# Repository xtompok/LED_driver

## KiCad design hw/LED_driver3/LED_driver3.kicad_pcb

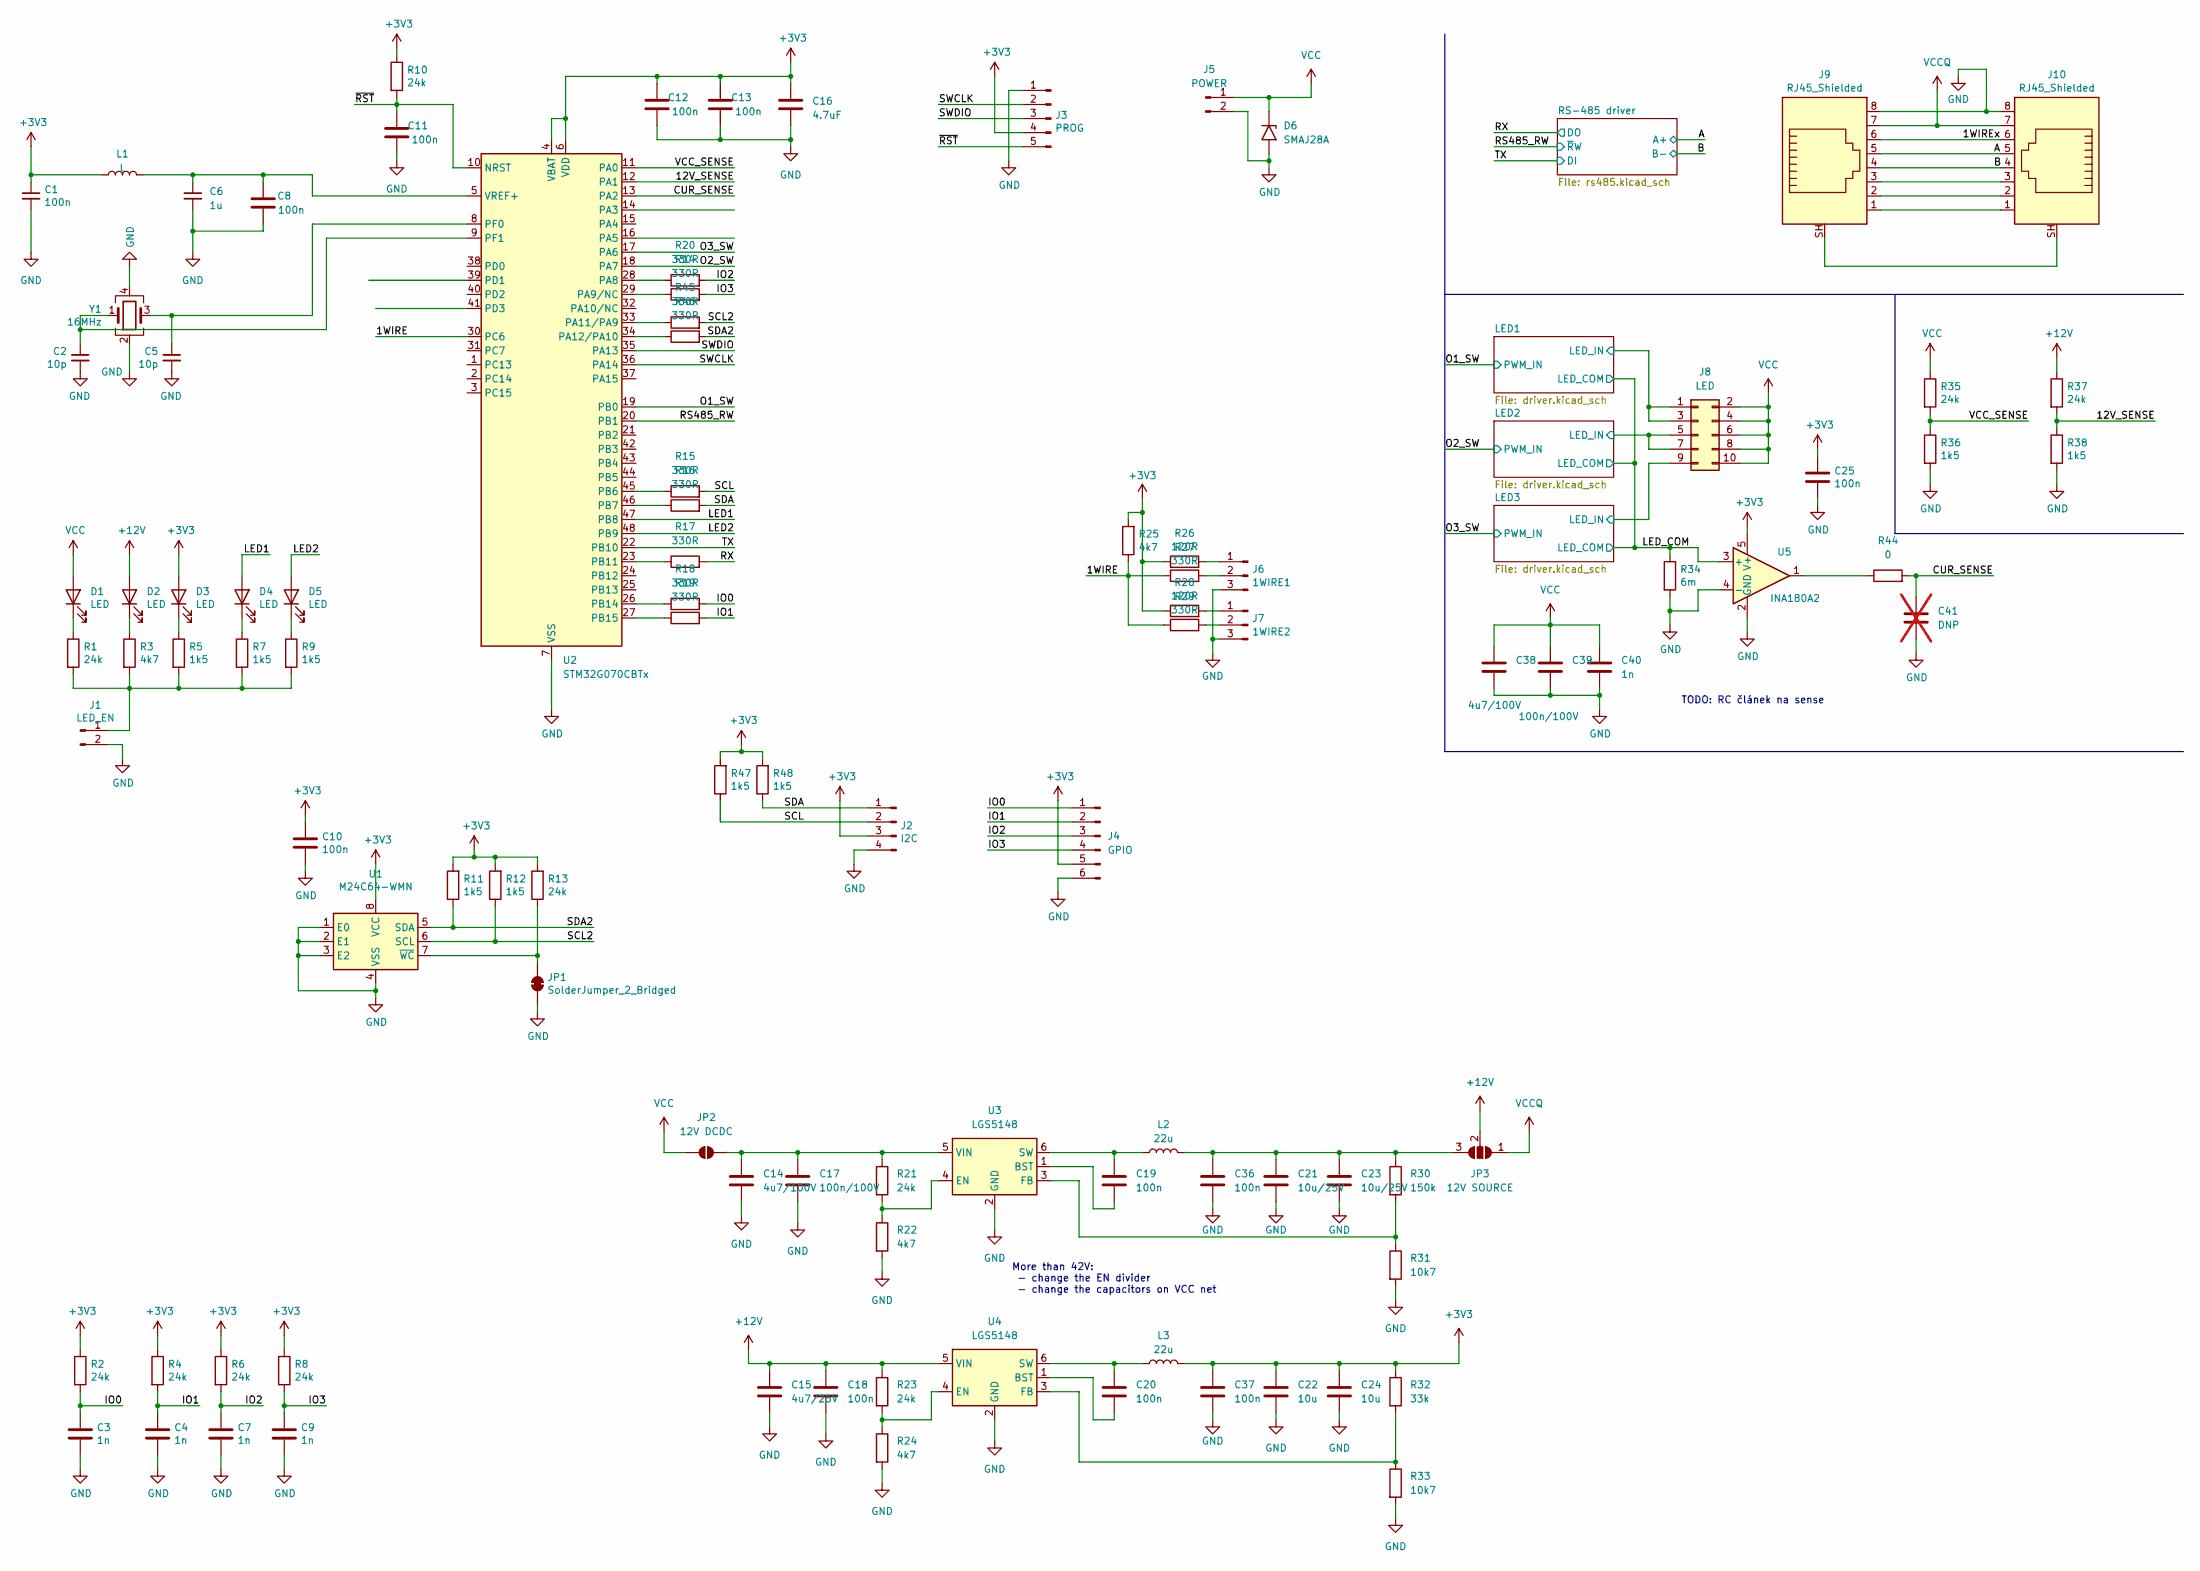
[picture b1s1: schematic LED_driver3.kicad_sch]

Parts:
C1: 100n; C_0603_1608Metric; Manufacturer_Part_Number CC0603KRX7R9BB104; LCSC C14663
C2, C5: 10p; C_0402_1005Metric; LCSC C32949
C3, C4, C7, C9, C40: 1n; C_0603_1608Metric; LCSC C1588
C6: 1u; C_0805_2012Metric; Manufacturer_Part_Number CL21B105KBFNNNE; LCSC C28323
C8, C10, C11, C12, C13, C18, C19, C20, C25, C36, C37: 100n; C_0603_1608Metric; LCSC C14663
C14, C38: 4u7/100V; C_1206_3216Metric; LCSC C29823
C15: 4u7/25V; C_0805_2012Metric; LCSC C1779
C16: 4.7uF; C_0603_1608Metric; LCSC C19666
C17, C39: 100n/100V; C_0805_2012Metric; LCSC C28233
C21, C23: 10u/25V; C_0805_2012Metric; LCSC C440198
C22, C24: 10u; C_0805_2012Metric; LCSC C440198
C41: DNP; C_0603_1608Metric; not fitted
D1: LED; LED_0603_1608Metric; LCSC C72043
D2, D3, D4, D5: LED; LED_0603_1608Metric
D6: SMAJ28A; D_SMA; LCSC C908775
J1: LED_EN; SolderJumper-2_P1.3mm_Open_TrianglePad1.0x1.5mm
J2: I2C; 15EDGVC-2.5-04P-14
J3: PROG; Molex_KK-254_AE-6410-05A_1x05_P2.54mm_Vertical
J4: GPIO; 15EDGVC-2.5-06P-14
J5: POWER; PhoenixContact_MSTB_2,5_2-GF-5,08_1x02_P5.08mm_Horizontal_T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
J6: 1WIRE1; 15EDGVC-2.5-03P-14
J7: 1WIRE2; 15EDGVC-2.5-03P-14
J8: LED; 15EDGRHCM-THR-3,50-10P-13
J9, J10: RJ45_Shielded; RJJS-88-A22-E1V
JP1: SolderJumper_2_Bridged; SolderJumper-2_P1.3mm_Bridged_Pad1.0x1.5mm
JP2: 12V DCDC; SolderJumper-2_P1.3mm_Open_TrianglePad1.0x1.5mm
JP3: 12V SOURCE; SolderJumper-3_P2.0mm_Open_TrianglePad1.0x1.5mm
L1: L; L_0805_2012Metric; LCSC C88990
L2, L3: 22u; L_Sunlord_SWPA4030S; LCSC C83472
R1, R2, R4, R6, R8, R10, R13, R21, R23, R35, R37: 24k; R_0603_1608Metric; LCSC C23352
R3, R22, R24, R25: 4k7; R_0603_1608Metric; LCSC C23162
R5, R7, R9, R11, R12, R36, R38, R47, R48: 1k5; R_0603_1608Metric; LCSC C22843
R14, R15, R16, R17, R18, R19, R20, R27, R29, R45, R46: 330R; R_0603_1608Metric; LCSC C23138
R26, R28: 120R; R_0603_1608Metric; LCSC C22787
R30: 150k; R_0603_1608Metric
R31, R33: 10k7; R_0603_1608Metric
R32: 33k; R_0603_1608Metric
R34: 6m; R_2512_6332Metric; LCSC C728340
R44: 0; R_0603_1608Metric
U1: M24C64-WMN; SOIC-8_3.9x4.9mm_P1.27mm; LCSC C79988
U2: STM32G070CBTx; LQFP-48_7x7mm_P0.5mm; LCSC C529338
U3, U4: LGS5148; SOT-23-6
U5: INA180A2; SOT-23-5; LCSC C192764
Y1: 16MHz; Crystal_SMD_3225-4Pin_3.2x2.5mm; LCSC C13738

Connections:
+3V3: C1.1, C10.1, C12.1, C13.1, C16.1, C22.1, C24.1, C25.1, C37.1, D3.2 (A), J2.3, J3.4, J4.5, L1.1, L3.2, R2.1, R4.1, R6.1, R8.1, R10.1, R11.2, R12.2, R13.2, R25.2, R26.1, R28.1, R32.1, R47.2, R48.2, U1.8 (VCC), U2.4 (VBAT), U2.6 (VDD), U5.5 (V+); also elsewhere on the board
+12V: C15.1, C18.1, D2.2 (A), JP3.2 (C), R23.1, R37.1, U4.5 (VIN); also elsewhere on the board
/1WIRE: R25.1, R27.1, R29.1, U2.30 (PC6)
/1WIREx: J9.6, J10.6
/12V_SENSE: R37.2, R38.1, U2.12 (PA1)
/A: J9.5, J10.5; also elsewhere on the board
/B: J9.4, J10.4; also elsewhere on the board
/CUR_SENSE: C41.1, R44.2, U2.13 (PA2)
/IO0: C3.2, J4.1, R2.2, R18.2
/IO1: C4.2, J4.2, R4.2, R19.2
/IO2: C7.2, J4.3, R6.2, R20.2
/IO3: C9.2, J4.4, R8.2, R14.2
/LED1: D4.2 (A), U2.47 (PB8)
/LED1/LED_IN: J8.1, J8.3; also elsewhere on the board
/LED2: D5.2 (A), U2.48 (PB9)
/LED2/LED_IN: J8.5, J8.7; also elsewhere on the board
/LED3/LED_IN: J8.9; also elsewhere on the board
/LED_COM: R34.1, U5.3 (+); also elsewhere on the board
/O1_SW: U2.19 (PB0); also elsewhere on the board
/O2_SW: U2.18 (PA7); also elsewhere on the board
/O3_SW: U2.17 (PA6); also elsewhere on the board
/RS485_RW: U2.20 (PB1); also elsewhere on the board
/RX: R17.2; also elsewhere on the board
/SCL: J2.2, R15.2, R47.1
/SCL2: R12.1, R45.2, U1.6 (SCL)
/SDA: J2.1, R16.2, R48.1
/SDA2: R11.1, R46.2, U1.5 (SDA)
/SWCLK: J3.2, U2.36 (PA14)
/SWDIO: J3.3, U2.35 (PA13)
/TX: U2.22 (PB10); also elsewhere on the board
/VCC_SENSE: R35.2, R36.1, U2.11 (PA0)
/~RST: C11.1, J3.5, R10.2, U2.10 (NRST)
GND: C1.2, C2.2, C3.1, C4.1, C5.2, C6.2, C7.1, C8.2, C9.1, C10.2, C11.2, C12.2, C13.2, C14.2, C15.2, C16.2, C17.2, C18.2, C21.2, C22.2, C23.2, C24.2, C25.2, C36.2, C37.2, C38.2, C39.2, C40.2, C41.2, D6.2 (A2), J1.2, J2.4, J3.1, J4.6, J5.2, J6.3, J7.3, J9.8, J10.8, JP1.2 (B), R22.2, R24.2, R31.2, R33.2, R34.2, R36.2, R38.2, U1.1 (E0), U1.2 (E1), U1.3 (E2), U1.4 (VSS), U2.7 (VSS), U3.2 (GND), U4.2 (GND), U5.2 (GND), U5.4 (-), Y1.2, Y1.4; also elsewhere on the board
unnamed: D1.1 (K), R1.1
unnamed: D2.1 (K), R3.1
unnamed: D3.1 (K), R5.1
unnamed: D4.1 (K), R7.1
unnamed: D5.1 (K), R9.1
unnamed: J1.1, R1.2, R3.2, R5.2, R7.2, R9.2
unnamed: J6.1, R26.2
unnamed: J6.2, R27.2
unnamed: J7.1, R28.2
unnamed: J7.2, R29.2
unnamed: J9.1, J10.1
unnamed: J9.2, J10.2
unnamed: J9.3, J10.3
unnamed: J9.SH, J10.SH
unnamed: JP1.1 (A), R13.1, U1.7 (~WC)
unnamed: C14.1, C17.1, JP2.2 (B), R21.1, U3.5 (VIN)
unnamed: C21.1, C23.1, C36.1, JP3.3 (B), L2.2, R30.1
unnamed: R44.1, U5.1
unnamed: R20.1, U2.28 (PA8)
unnamed: R14.1, U2.29 (PA9/NC)
unnamed: R45.1, U2.33 (PA11/PA9)
unnamed: R46.1, U2.34 (PA12/PA10)
unnamed: R15.1, U2.45 (PB6)
unnamed: R16.1, U2.46 (PB7)
unnamed: R17.1, U2.23 (PB11)
unnamed: R18.1, U2.26 (PB14)
unnamed: R19.1, U2.27 (PB15)
unnamed: C5.1, U2.8 (PF0), Y1.3
unnamed: C2.1, U2.9 (PF1), Y1.1
unnamed: C6.1, C8.1, L1.2, U2.5 (VREF+)
unnamed: C19.2, U3.1 (BST)
unnamed: R21.2, R22.1, U3.4 (EN)
unnamed: R30.2, R31.1, U3.3 (FB)
unnamed: C19.1, L2.1, U3.6 (SW)
unnamed: C20.2, U4.1 (BST)
unnamed: R23.2, R24.1, U4.4 (EN)
unnamed: R32.2, R33.1, U4.3 (FB)
unnamed: C20.1, L3.1, U4.6 (SW)
VCC: C38.1, C39.1, C40.1, D1.2 (A), D6.1 (A1), J5.1, J8.2, J8.4, J8.6, J8.8, J8.10, JP2.1 (A), R35.1; also elsewhere on the board
VCCQ: J9.7, J10.7, JP3.1 (A)

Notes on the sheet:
More than 42V: - change the EN divider - change the capacitors on VCC net
TODO: RC článek na sense

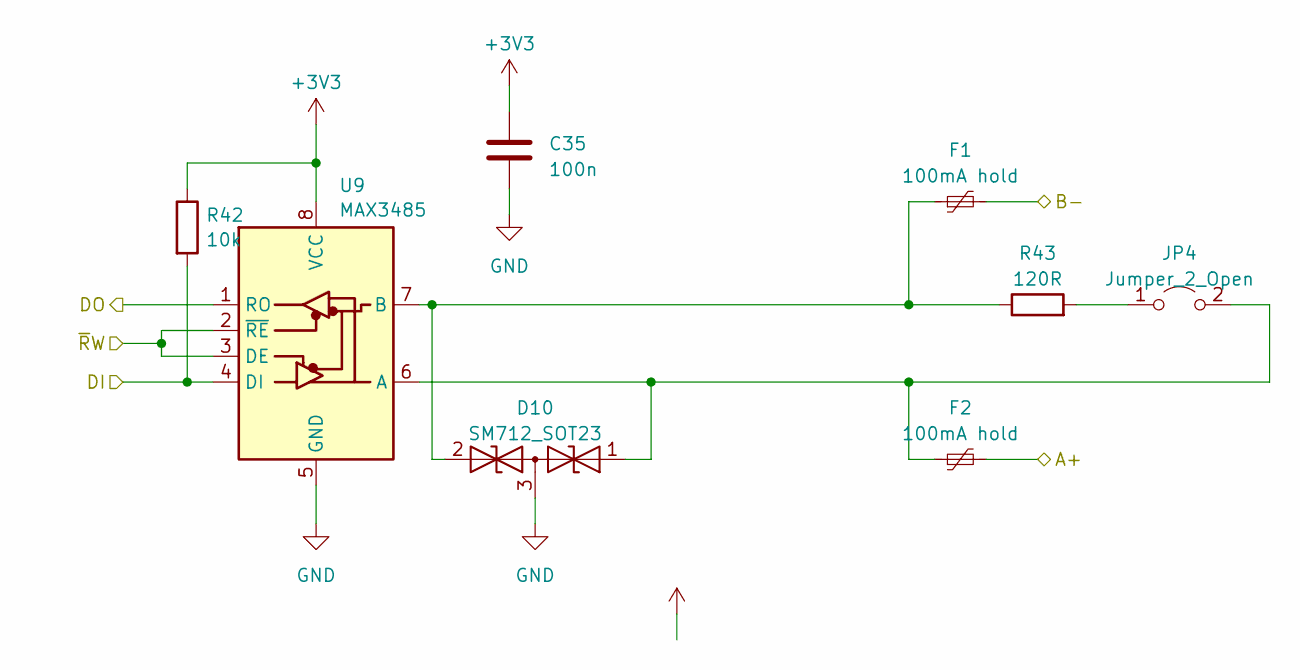
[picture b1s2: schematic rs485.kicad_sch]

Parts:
C35: 100n; C_0603_1608Metric; LCSC C14663
D10: SM712_SOT23; SOT-23; LCSC C404012
F1, F2: 100mA hold; Fuse_1206_3216Metric; LCSC C70065
JP4: Jumper_2_Open; SolderJumper-2_P1.3mm_Open_TrianglePad1.0x1.5mm; LCSC XXXX
R42: 10k; R_0603_1608Metric; LCSC C25804
R43: 120R; R_0603_1608Metric; LCSC C22787
U9: MAX3485; SOIC-8_3.9x4.9mm_P1.27mm; LCSC C8963

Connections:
+3V3: C35.1, R42.1, U9.8 (VCC); also elsewhere on the board
/A: F2.2; also elsewhere on the board
/B: F1.2; also elsewhere on the board
/RS485_RW: U9.2 (~RE), U9.3 (DE); also elsewhere on the board
/RX: U9.1 (RO); also elsewhere on the board
/TX: R42.2, U9.4 (DI); also elsewhere on the board
GND: C35.2, D10.3 (common), U9.5 (GND); also elsewhere on the board
unnamed: D10.1 (A1), F2.1, JP4.2 (B), U9.6 (A)
unnamed: D10.2 (A2), F1.1, R43.1, U9.7 (B)
unnamed: JP4.1 (A), R43.2

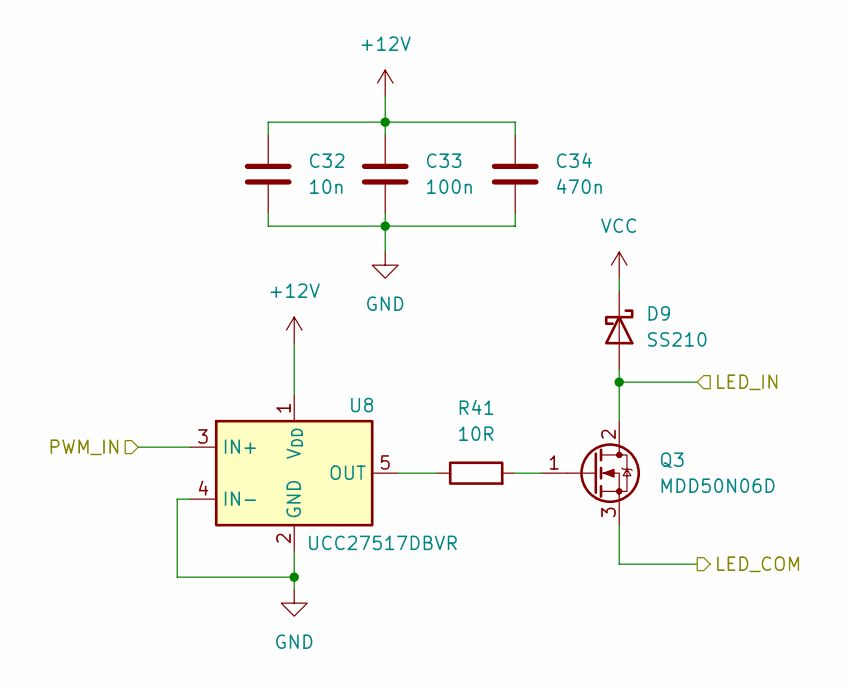
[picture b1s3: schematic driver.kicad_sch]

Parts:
C32: 10n; C_0603_1608Metric; LCSC C57112
C33: 100n; C_0603_1608Metric; LCSC C14663
C34: 470n; C_0603_1608Metric; LCSC C1623
D9: SS210; D_SMA; LCSC C14996
Q3: MDD50N06D; TO-252-2; LCSC C99395
R41: 10R; R_0603_1608Metric; LCSC C22859
U8: UCC27517DBVR; SOT-23-5

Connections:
+12V: C32.1, C33.1, C34.1, U8.1 (V_{DD}); also elsewhere on the board
/LED3/LED_IN: D9.2 (A), Q3.2 (D); also elsewhere on the board
/LED_COM: Q3.3 (S); also elsewhere on the board
/O3_SW: U8.3 (IN+); also elsewhere on the board
GND: C32.2, C33.2, C34.2, U8.2 (GND), U8.4 (IN-); also elsewhere on the board
unnamed: Q3.1 (G), R41.2
unnamed: R41.1, U8.5 (OUT)
VCC: D9.1 (K); also elsewhere on the board

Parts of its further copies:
C26, C29: 10n; C_0603_1608Metric; LCSC C57112
C27, C30: 100n; C_0603_1608Metric; LCSC C14663
C28, C31: 470n; C_0603_1608Metric; LCSC C1623
D7, D8: SS210; D_SMA; LCSC C14996
Q1, Q2: MDD50N06D; TO-252-2; LCSC C99395
R39, R40: 10R; R_0603_1608Metric; LCSC C22859
U6, U7: UCC27517DBVR; SOT-23-5

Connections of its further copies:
+12V: C26.1, C27.1, C28.1, C29.1, C30.1, C31.1, U6.1 (V_{DD}), U7.1 (V_{DD}); also elsewhere on the board
/LED1/LED_IN: D7.2 (A), Q1.2 (D); also elsewhere on the board
/LED2/LED_IN: D8.2 (A), Q2.2 (D); also elsewhere on the board
/LED_COM: Q1.3 (S), Q2.3 (S); also elsewhere on the board
/O1_SW: U6.3 (IN+); also elsewhere on the board
/O2_SW: U7.3 (IN+); also elsewhere on the board
GND: C26.2, C27.2, C28.2, C29.2, C30.2, C31.2, U6.2 (GND), U6.4 (IN-), U7.2 (GND), U7.4 (IN-); also elsewhere on the board
unnamed: Q1.1 (G), R39.2
unnamed: Q2.1 (G), R40.2
unnamed: R39.1, U6.5 (OUT)
unnamed: R40.1, U7.5 (OUT)
VCC: D7.1 (K), D8.1 (K); also elsewhere on the board

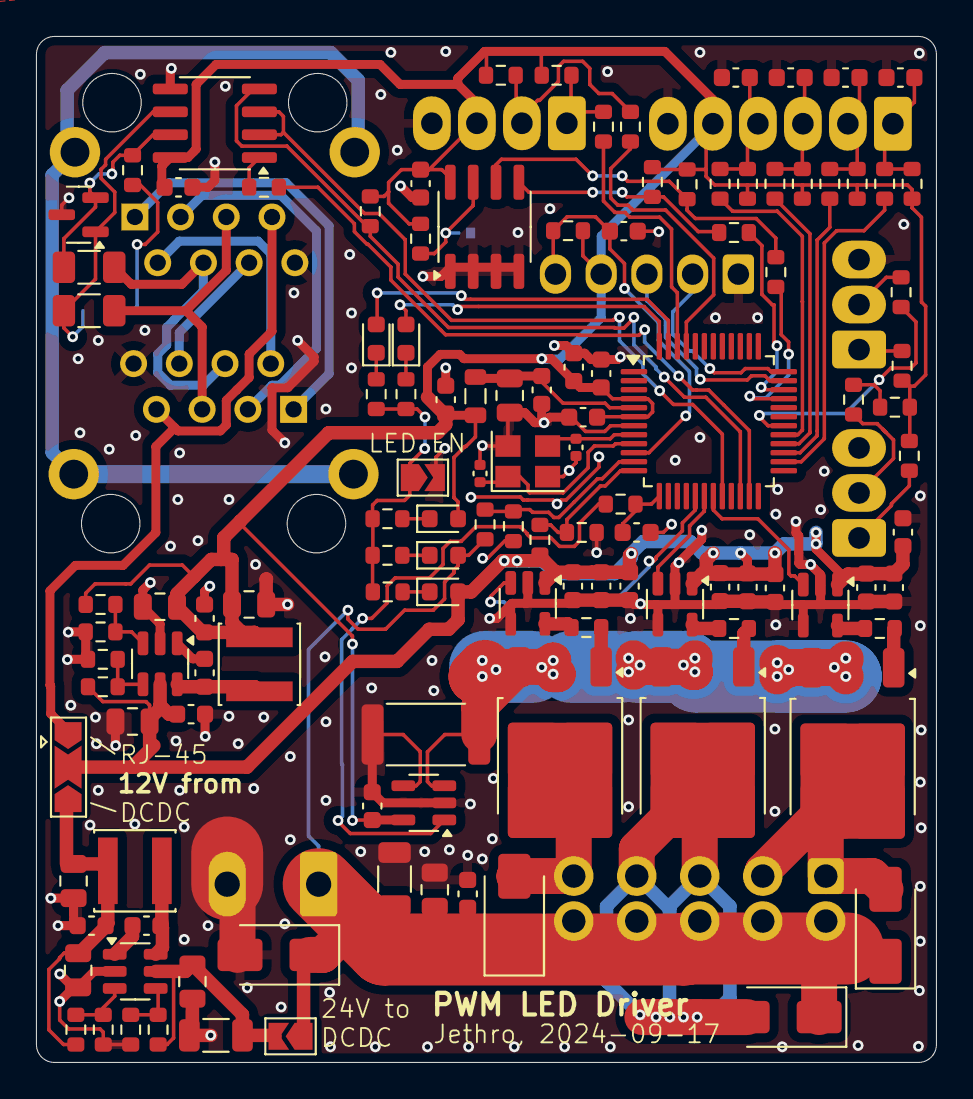
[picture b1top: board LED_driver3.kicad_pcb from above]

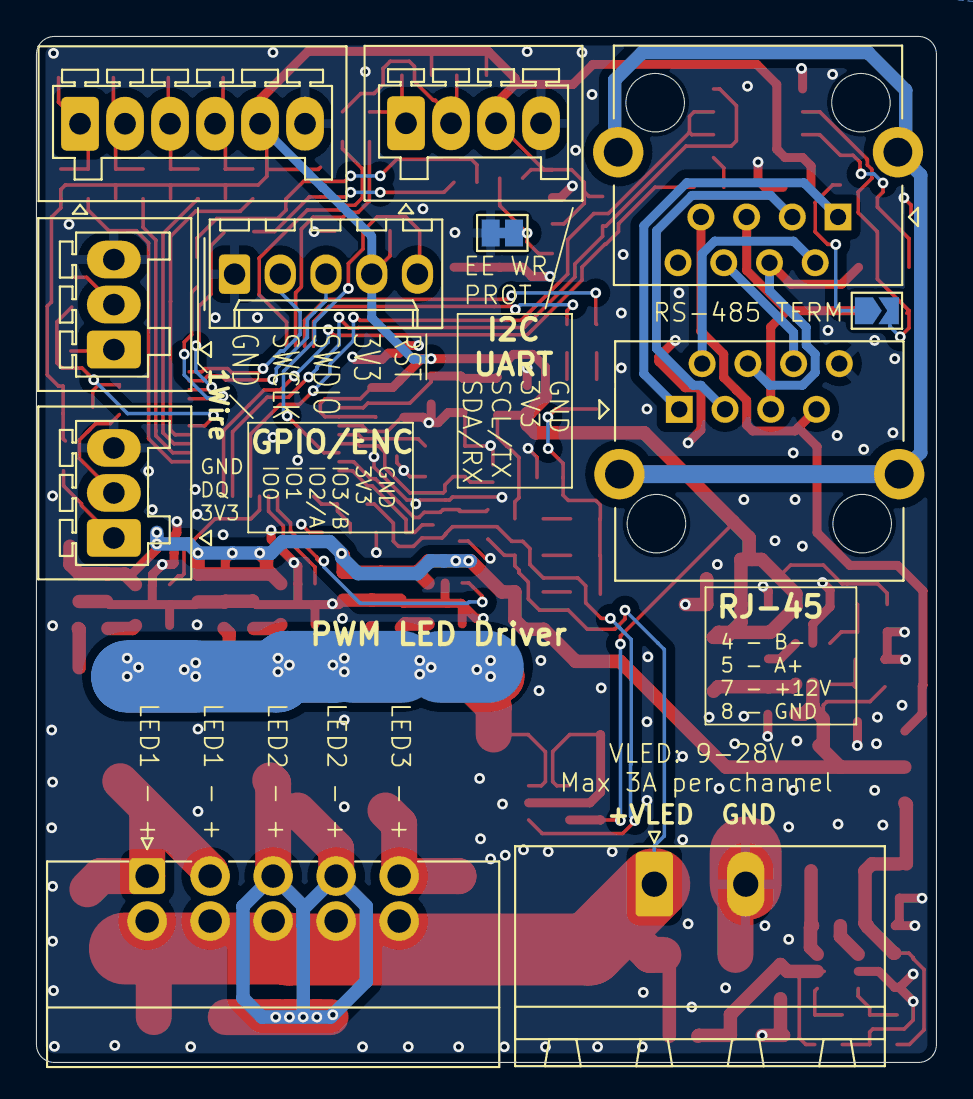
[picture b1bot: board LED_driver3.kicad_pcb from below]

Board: 2 copper layers, 50.0 x 57.0 mm, 131 parts (11 on the bottom side), 82 nets.

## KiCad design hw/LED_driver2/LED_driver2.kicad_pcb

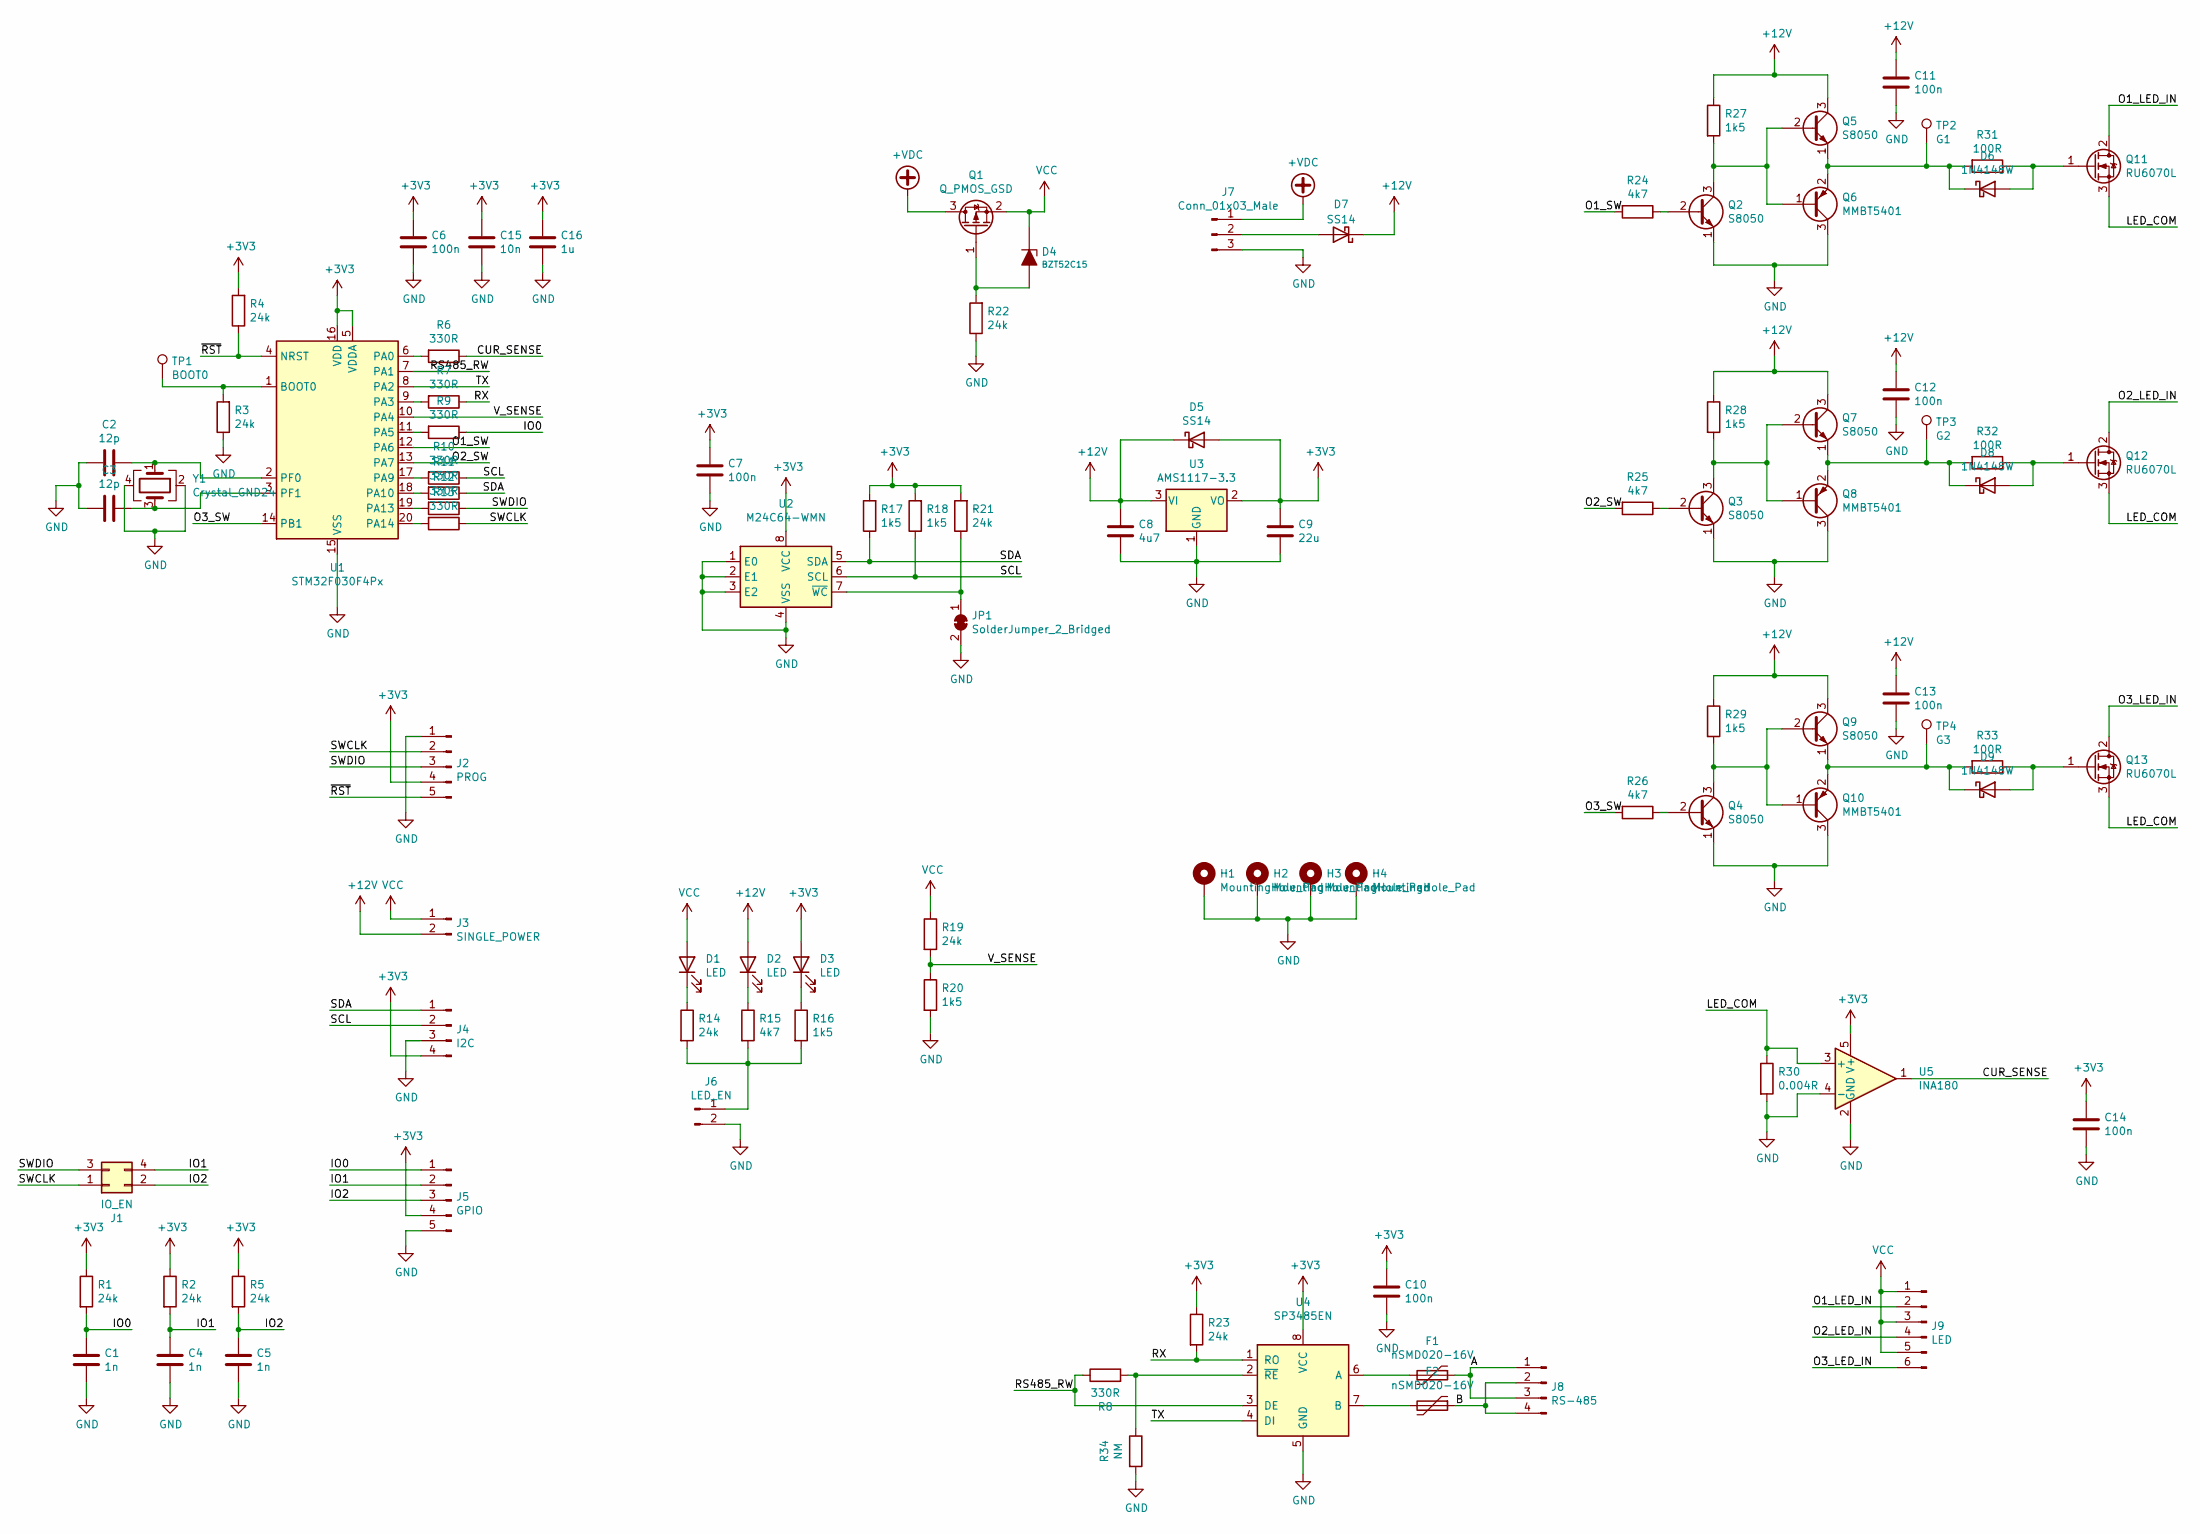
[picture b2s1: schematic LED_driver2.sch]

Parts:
C1: 1n; C_0603_1608Metric; LCSC C1588
C2: 12p; C_0603_1608Metric; LCSC C38523
C3: 12p; C_0603_1608Metric
C4, C5: 1n; C_0603_1608Metric
C6, C7, C10: 100n; C_0603_1608Metric
C8: 4u7; C_0603_1608Metric; LCSC C19666
C9: 22u; C_0603_1608Metric; LCSC C59461
C11: 100n; R_0603_1608Metric; LCSC C14663
C12, C13: 100n; R_0603_1608Metric
C14: 100n; C_0603_1608Metric; LCSC C14663
C15: 10n; C_0603_1608Metric; LCSC C57112
C16: 1u; C_0603_1608Metric; LCSC C15849
D1: LED; LED_0603_1608Metric; LCSC C72043
D2, D3: LED; LED_0603_1608Metric
D4: BZT52C15; D_SOD-123
D5: SS14; D_SMA
D6, D8, D9: 1N4148W; D_SOD-123; LCSC C81598
D7: SS14; D_SMA; LCSC C2480
F1, F2: nSMD020-16V; Fuse_1206_3216Metric
H1, H2, H3, H4: MountingHole_Pad; MountingHole_3.2mm_M3_Pad_Via
J1: IO_EN; PinHeader_2x02_P2.54mm_Vertical
J2: PROG; Molex_KK-254_AE-6410-05A_1x05_P2.54mm_Vertical
J3: SINGLE_POWER; PinHeader_2x01_P2.54mm_Vertical
J4: I2C; Molex_KK-254_AE-6410-04A_1x04_P2.54mm_Vertical
J5: GPIO; PTSA_1.5_5-3.5-Z_1985221
J6: LED_EN; PinHeader_1x02_P2.54mm_Vertical
J7: Conn_01x03_Male; PhoenixContact_MSTB_2,5_3-GF-5,08_1x03_P5.08mm_Horizontal_T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
J8: RS-485; PTSA_1.5_4-3.5-Z-1985218
J9: LED; PTSA_1.5_6-3.5-Z-1985234
JP1: SolderJumper_2_Bridged; SolderJumper-2_P1.3mm_Bridged_Pad1.0x1.5mm
Q1: Q_PMOS_GSD; TO-252-2
Q2, Q3, Q5, Q7, Q9: S8050; SOT-23
Q4: S8050; SOT-23; LCSC C2146
Q6, Q8: MMBT5401; SOT-23
Q10: MMBT5401; SOT-23; LCSC C8326
Q11, Q12, Q13: RU6070L; TO-252-2
R1, R2, R3, R5, R14, R19, R21, R22, R23: 24k; R_0603_1608Metric
R4: 24k; R_0603_1608Metric; LCSC C23352
R6: 330R; R_0603_1608Metric; LCSC C23138
R7, R8, R9, R10, R11, R12, R13: 330R; R_0603_1608Metric
R15, R25, R26: 4k7; R_0603_1608Metric
R16, R18, R20, R27, R28, R29: 1k5; R_0603_1608Metric
R17: 1k5; R_0603_1608Metric; LCSC C22843
R24: 4k7; R_0603_1608Metric; LCSC C23162
R30: 0.004R; R_2512_6332Metric
R31: 100R; R_0603_1608Metric; LCSC C22775
R32, R33: 100R; R_0603_1608Metric
R34: NM; R_0603_1608Metric
TP1: BOOT0; TestPoint_THTPad_D2.0mm_Drill1.0mm
TP2: G1; TestPoint_THTPad_D1.0mm_Drill0.5mm
TP3: G2; TestPoint_THTPad_D1.0mm_Drill0.5mm
TP4: G3; TestPoint_THTPad_D1.0mm_Drill0.5mm
U1: STM32F030F4Px; TSSOP-20_4.4x6.5mm_P0.65mm
U2: M24C64-WMN; SOIC-8_3.9x4.9mm_P1.27mm; LCSC C79988
U3: AMS1117-3.3; SOT-223-3_TabPin2; LCSC C6186
U4: SP3485EN; SOIC-8_3.9x4.9mm_P1.27mm; LCSC C8963
U5: INA180; SOT-23-5
Y1: Crystal_GND24; Crystal_SMD_3225-4Pin_3.2x2.5mm; LCSC C13738

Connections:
+3V3: C6.1, C7.1, C9.1, C10.1, C14.1, C15.1, C16.1, D3.2 (A), D5.2 (A), J2.4, J4.4, J5.4, R1.1, R2.1, R4.2, R5.1, R17.2, R18.2, R21.2, R23.1, U1.5 (VDDA), U1.16 (VDD), U2.8 (VCC), U3.2 (VO), U4.8 (VCC), U5.5 (V+)
+12V: C8.1, C11.1, C12.1, C13.1, D2.2 (A), D5.1 (K), D7.1 (K), J3.2, Q5.3 (C), Q7.3 (C), Q9.3 (C), R27.1, R28.1, R29.1, U3.3 (VI)
+VDC: J7.1, Q1.3 (D)
/A: F1.1, J8.1, J8.3
/B: F2.1, J8.2, J8.4
/CUR_SENSE: R6.1, U5.1
/IO0: C1.2, J5.1, R1.2, R9.1
/IO1: C4.2, J1.4, J5.2, R2.2
/IO2: C5.2, J1.2, J5.3, R5.2
/LED_COM: Q11.3 (S), Q12.3 (S), Q13.3 (S), R30.1, U5.3 (+)
/O1_LED_IN: J9.2, Q11.2 (D)
/O1_SW: R24.2, U1.12 (PA6)
/O2_LED_IN: J9.4, Q12.2 (D)
/O2_SW: R25.2, U1.13 (PA7)
/O3_LED_IN: J9.6, Q13.2 (D)
/O3_SW: R26.2, U1.14 (PB1)
/RS485_RW: R8.1, U1.7 (PA1), U4.3 (DE)
/RX: R7.1, R23.2, U4.1 (RO)
/SCL: J4.2, R10.1, R18.1, U2.6 (SCL)
/SDA: J4.1, R11.1, R17.1, U2.5 (SDA)
/SWCLK: J1.1, J2.2, R13.1
/SWDIO: J1.3, J2.3, R12.1
/TX: U1.8 (PA2), U4.4 (DI)
/V_SENSE: R19.2, R20.1, U1.10 (PA4)
/~RST: J2.5, R4.1, U1.4 (NRST)
GND: C1.1, C2.2, C3.2, C4.1, C5.1, C6.2, C7.2, C8.2, C9.2, C10.2, C11.2, C12.2, C13.2, C14.2, C15.2, C16.2, H1.1, H2.1, H3.1, H4.1, J2.1, J4.3, J5.5, J6.2, J7.3, JP1.2 (B), Q2.1 (E), Q3.1 (E), Q4.1 (E), Q6.3 (C), Q8.3 (C), Q10.3 (C), R3.1, R20.2, R22.1, R30.2, R34.2, U1.15 (VSS), U2.1 (E0), U2.2 (E1), U2.3 (E2), U2.4 (VSS), U3.1 (GND), U4.5 (GND), U5.2 (GND), U5.4 (-), Y1.2, Y1.4
unnamed: C2.1, U1.2 (PF0), Y1.1
unnamed: C3.1, U1.3 (PF1), Y1.3
unnamed: D1.1 (K), R14.1
unnamed: D2.1 (K), R15.1
unnamed: D3.1 (K), R16.1
unnamed: D4.1 (A), Q1.1 (G), R22.2
unnamed: D6.1 (K), Q5.1 (E), Q6.2 (E), R31.2, TP2.1
unnamed: D6.2 (A), Q11.1 (G), R31.1
unnamed: D7.2 (A), J7.2
unnamed: D8.1 (K), Q7.1 (E), Q8.2 (E), R32.2, TP3.1
unnamed: D8.2 (A), Q12.1 (G), R32.1
unnamed: D9.1 (K), Q9.1 (E), Q10.2 (E), R33.2, TP4.1
unnamed: D9.2 (A), Q13.1 (G), R33.1
unnamed: F1.2, U4.6 (A)
unnamed: F2.2, U4.7 (B)
unnamed: J6.1, R14.2, R15.2, R16.2
unnamed: JP1.1 (A), R21.1, U2.7 (~WC)
unnamed: Q2.2 (B), R24.1
unnamed: Q2.3 (C), Q5.2 (B), Q6.1 (B), R27.2
unnamed: Q3.2 (B), R25.1
unnamed: Q3.3 (C), Q7.2 (B), Q8.1 (B), R28.2
unnamed: Q4.2 (B), R26.1
unnamed: Q4.3 (C), Q9.2 (B), Q10.1 (B), R29.2
unnamed: R3.2, TP1.1, U1.1 (BOOT0)
unnamed: R6.2, U1.6 (PA0)
unnamed: R7.2, U1.9 (PA3)
unnamed: R9.2, U1.11 (PA5)
unnamed: R10.2, U1.17 (PA9)
unnamed: R11.2, U1.18 (PA10)
unnamed: R12.2, U1.19 (PA13)
unnamed: R13.2, U1.20 (PA14)
unnamed: R8.2, R34.1, U4.2 (~RE~)
VCC: D1.2 (A), D4.2 (K), J3.1, J9.1, J9.3, J9.5, Q1.2 (S), R19.1

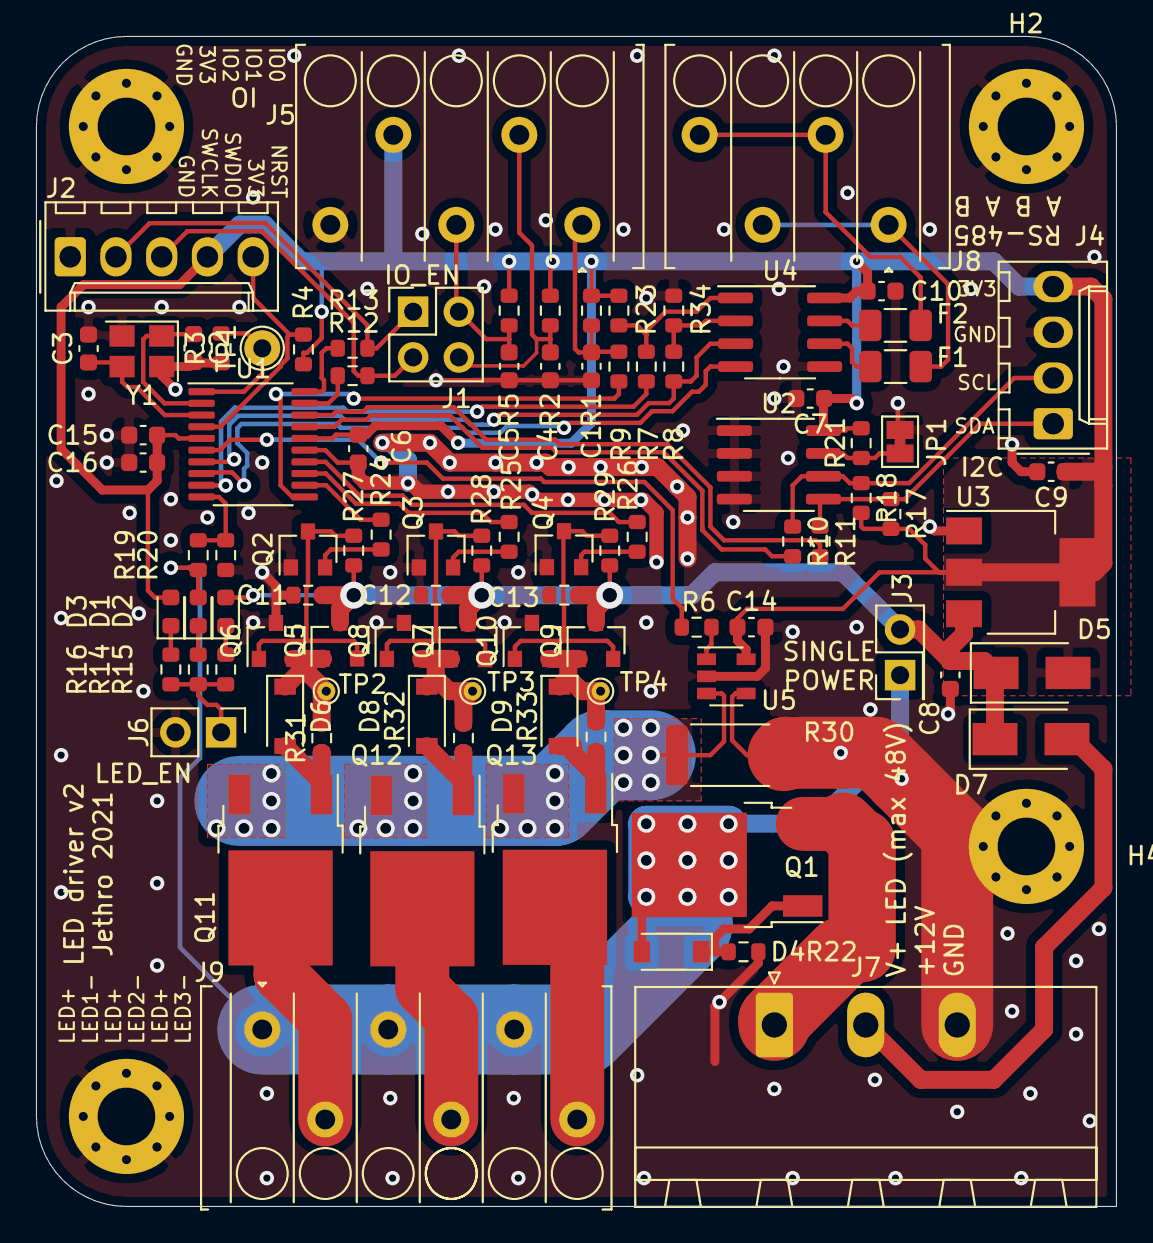
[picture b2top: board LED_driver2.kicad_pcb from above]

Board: 2 copper layers, 60.0 x 65.0 mm, 98 parts (0 on the bottom side), 59 nets.
